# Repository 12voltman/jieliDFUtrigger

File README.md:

# USB-C dongle for triggering DFU mode on Jieli-Tech microcontrollers  
These chips are primarily programmed over USB 2.0, and appear as mass-storage devices.  However, they do not have a traditional reset button and rely on a specific bit pattern being presented on the USB data lines.  
This project pulls heavily from the excellent research of @christian-kramer [here](https://github.com/christian-kramer/JieLi-AC690X-Familiarization).  

## How to use
TBD, will always let you trigger DFU using onboard button, may also have optional modes to automatically enter DFU when plugging in a board.

## Alternate uses
This board also breaks out some of the secondary USB-C lines (the CC and SBU pins) to a header, so you can use it to probe those lines.  
Several of my boards also use these lines for non-standard uses in ways that ideally don't conflict with the USB-C specifications.  Some examples include battery level monitoring, onewire debug, and firmware upload.  
In particular, some of my boards that inclue a modern ATTINY processor (including this one) bring the single wire programming interface (UPDI) out to the SBU pins of the female USB-C connector, so if I ever have to make 1000 of them I can upload the firmware with a tool such as this.  
For this application, and for updating the firmware of the ATTINY412 on this board, you can use a tool such as the [LV UPDI Friend](https://www.adafruit.com/product/5879) or [HV UPDI Friend](https://www.adafruit.com/product/5893) from Adafruit.  
For updating the onboard MCU, connect as following (UPDI Friend to this board) VCC to +, GND to -, and UPDI to the test point labeled UPDI.  
For using this tool with a UPDI Friend to update another board connected to it, connect as following, VCC to + (do not connect if powering over USB), GND to -, UPDI to SBU1.

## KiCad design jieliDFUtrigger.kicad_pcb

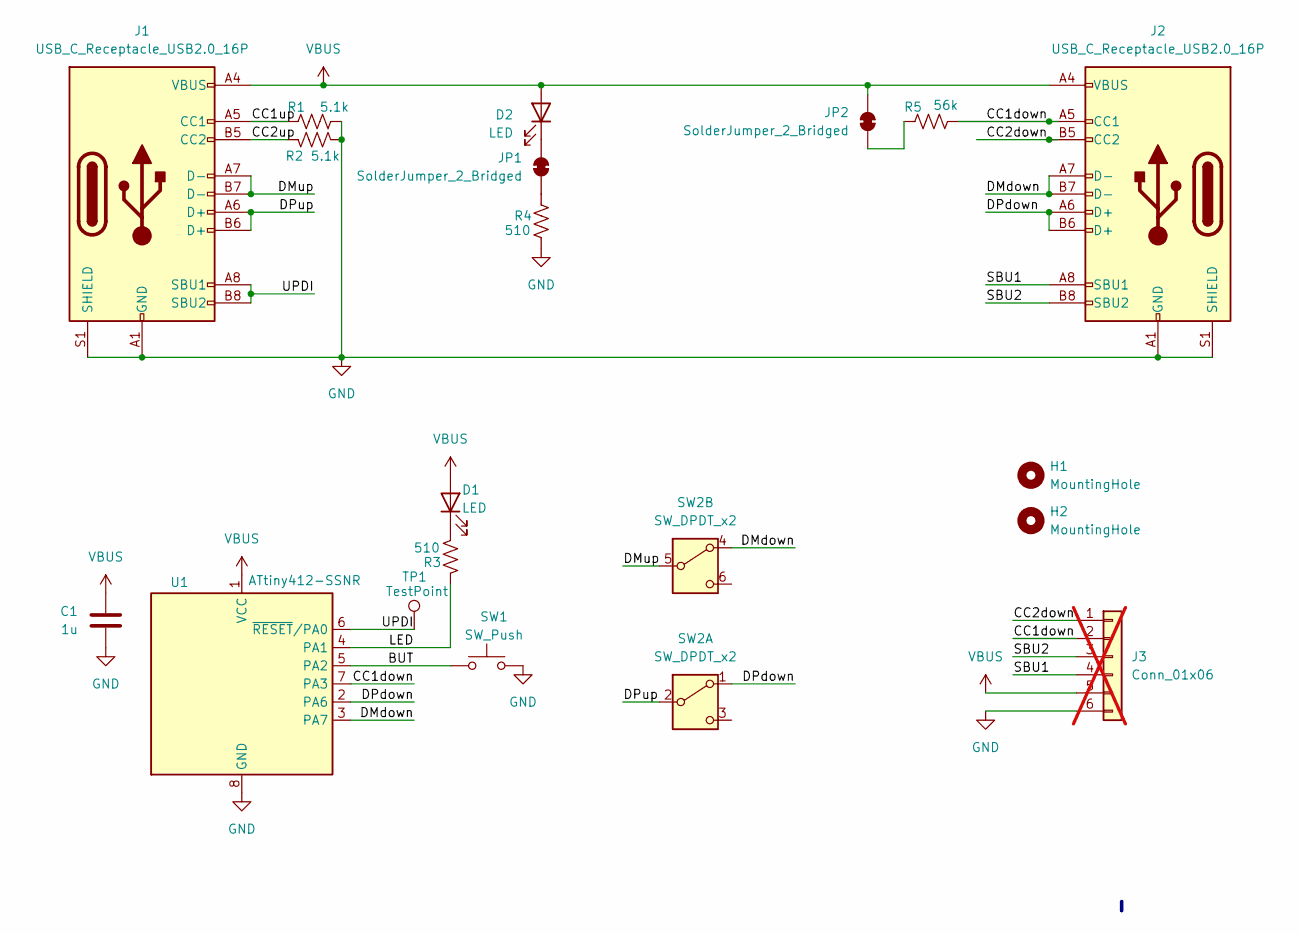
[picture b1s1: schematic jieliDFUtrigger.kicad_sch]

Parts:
C1: 1u; C_0402_1005Metric; LCSC C52923
D1: LED; LED_0402_1005Metric; LCSC C2856703
D2: LED; LED_0402_1005Metric; LCSC C965790
H1, H2: MountingHole; MountingHole_3.2mm_M3
J1: USB_C_Receptacle_USB2.0_16P; USB_C_Receptacle_HCTL_HC-TYPE-C-16P-01A; LCSC C2765186
J2: USB_C_Receptacle_USB2.0_16P; USB_C_PLUG_VERT_YTC-TC16S-128; LCSC C2927282
J3: Conn_01x06; PinHeader_1x06_P2.54mm_Vertical; LCSC C37208; not fitted
JP1, JP2: SolderJumper_2_Bridged; SolderJumper-2_P1.3mm_Bridged_RoundedPad1.0x1.5mm
R1, R2: 5.1k; R_0402_1005Metric; LCSC C25905
R3, R4: 510; R_0402_1005Metric; LCSC C25123
R5: 56k; R_0402_1005Metric; LCSC C25796
SW1: SW_Push; TINYTACTILE; LCSC C455280
SW2: SW_DPDT_x2; DPDT-Slide_top; LCSC C2837066
TP1: TestPoint; TestPoint_Pad_D3.0mm
U1: ATtiny412-SSNR; SOIC-8_3.9x4.9mm_P1.27mm; LCSC C1337190

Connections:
/BUT: SW1.1, U1.5 (PA2)
/CC1down: J2.A5 (CC1), J3.2, R5.2, U1.7 (PA3)
/CC1up: J1.A5 (CC1), R1.1
/CC2down: J2.B5 (CC2), J3.1
/CC2up: J1.B5 (CC2), R2.1
/DMdown: J2.A7 (D-), J2.B7 (D-), SW2.4 (A), U1.3 (PA7)
/DMup: J1.A7 (D-), J1.B7 (D-), SW2.5 (B)
/DPdown: J2.A6 (D+), J2.B6 (D+), SW2.1 (A), U1.2 (PA6)
/DPup: J1.A6 (D+), J1.B6 (D+), SW2.2 (B)
/LED: R3.2, U1.4 (PA1)
/SBU1: J2.A8 (SBU1), J3.4
/SBU2: J2.B8 (SBU2), J3.3
/UPDI: J1.A8 (SBU1), J1.B8 (SBU2), TP1.1, U1.6 (~RESET/PA0)
GND: C1.2, J1.A1 (GND), J1.A12 (GND), J1.B1 (GND), J1.B12 (GND), J1.S1 (SHIELD), J2.A1 (GND), J2.A12 (GND), J2.B1 (GND), J2.B12 (GND), J2.S1 (SHIELD), J3.6, R1.2, R2.2, R4.1, SW1.2, U1.8 (GND)
unnamed: D1.1 (K), R3.1
unnamed: D2.1 (K), JP1.1 (A)
unnamed: JP1.2 (B), R4.2
unnamed: JP2.2 (B), R5.1
VBUS: C1.1, D1.2 (A), D2.2 (A), J1.A4 (VBUS), J1.A9 (VBUS), J1.B4 (VBUS), J1.B9 (VBUS), J2.A4 (VBUS), J2.A9 (VBUS), J2.B4 (VBUS), J2.B9 (VBUS), J3.5, JP2.1 (A), U1.1 (VCC)

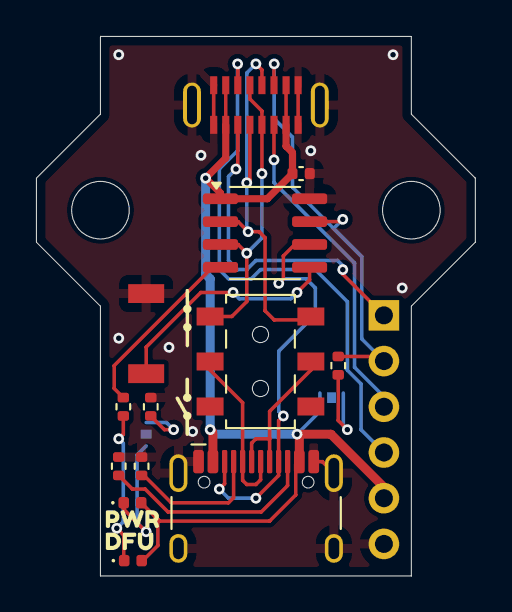
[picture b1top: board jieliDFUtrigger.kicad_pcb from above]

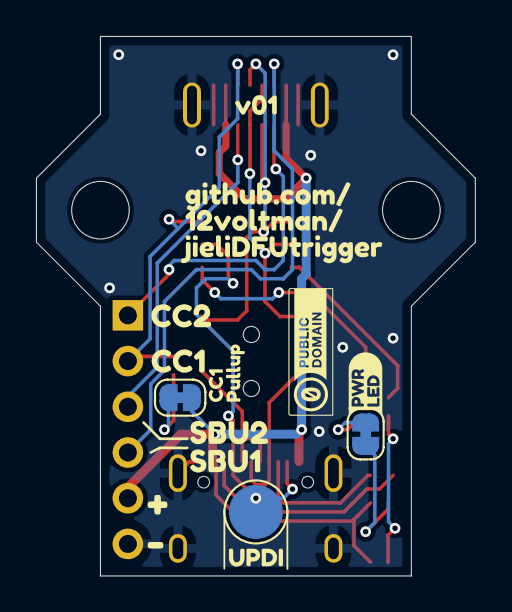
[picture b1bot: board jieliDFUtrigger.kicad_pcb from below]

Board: 2 copper layers, 24.4 x 30.0 mm, 29 parts (12 on the bottom side), 19 nets.

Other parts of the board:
kibuzzard-6680AAC4: G***; kibuzzard-6680AAC4
kibuzzard-668124E2: G***; kibuzzard-668124E2
kibuzzard-668145FF: G***; kibuzzard-668145FF
kibuzzard-668146A2: G***; kibuzzard-668146A2
kibuzzard-668148BC: G***; kibuzzard-668148BC
kibuzzard-6681489B: G***; kibuzzard-6681489B
kibuzzard-66814327: G***; kibuzzard-66814327
kibuzzard-66814765: G***; kibuzzard-66814765
kibuzzard-66814857: G***; kibuzzard-66814857
kibuzzard-66814893: G***; kibuzzard-66814893

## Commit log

2024-06-30 Initial PCB files
2024-07-01 Minor oversights
2024-07-12 Changed parts
